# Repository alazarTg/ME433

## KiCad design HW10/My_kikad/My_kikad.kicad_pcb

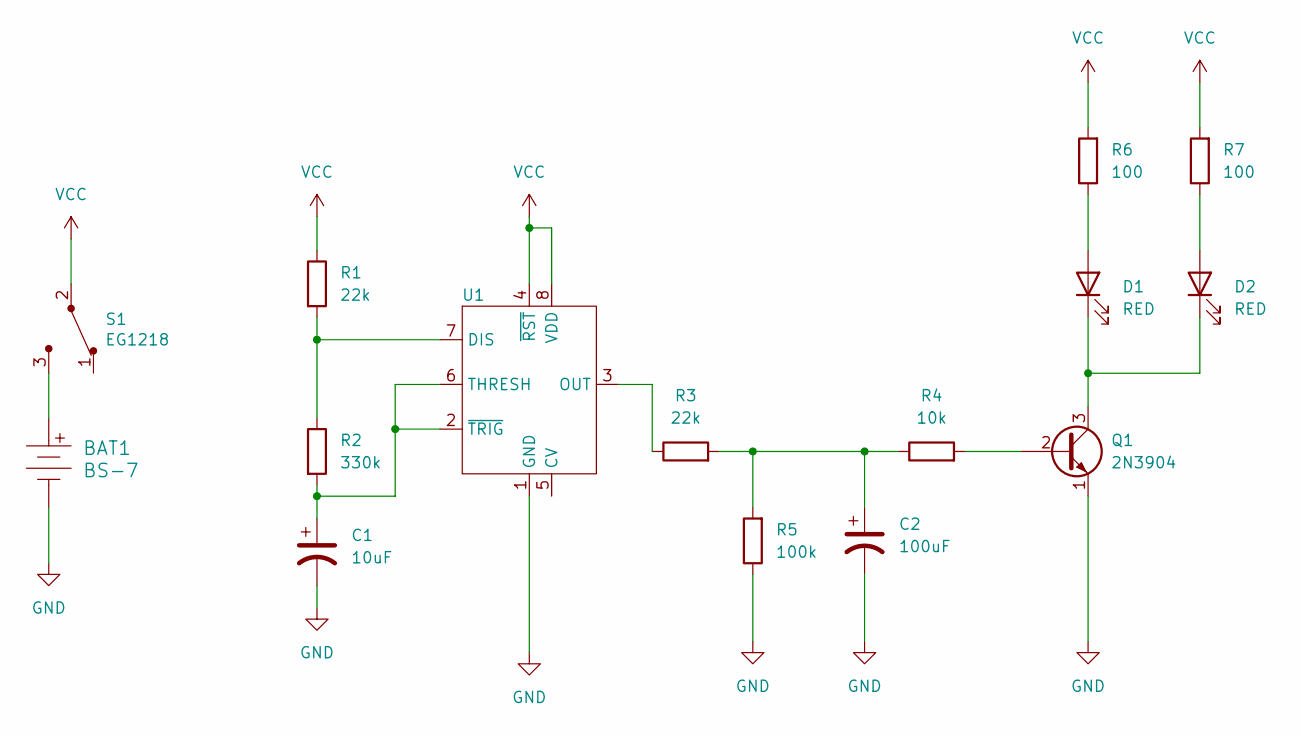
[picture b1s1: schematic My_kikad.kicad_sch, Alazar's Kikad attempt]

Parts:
BAT1: BS-7; Battery_Holder_Coin_2032_BS-7; MPN BS-7; Digi-Key_PN BS-7-ND
C1: 10uF; CP_Radial_D5.0mm_P2.00mm
C2: 100uF; CP_Radial_D6.3mm_P2.50mm
D1, D2: RED; LED_D3.0mm
Q1: 2N3904; TO-92-3
R1, R3: 22k; R_Axial_DIN0207_L6.3mm_D2.5mm_P7.62mm_Horizontal
R2: 330k; R_Axial_DIN0207_L6.3mm_D2.5mm_P7.62mm_Horizontal
R4: 10k; R_Axial_DIN0207_L6.3mm_D2.5mm_P7.62mm_Horizontal
R5: 100k; R_Axial_DIN0207_L6.3mm_D2.5mm_P7.62mm_Horizontal
R6, R7: 100; R_Axial_DIN0207_L6.3mm_D2.5mm_P7.62mm_Horizontal
S1: EG1218; Switch_Slide_11.6x4mm_EG1218; MPN EG1218; Digi-Key_PN EG1903-ND
U1: ICM7555_PDIP

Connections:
GND: BAT1.Neg, C1.2, C2.2, Q1.1 (E), R5.1, U1.1 (GND); also elsewhere on the board
unnamed: BAT1.Pos, S1.3
unnamed: C2.1, R3.2, R4.1, R5.2
unnamed: D1.2 (A), R6.1
unnamed: D1.1 (K), D2.1 (K), Q1.3 (C)
unnamed: D2.2 (A), R7.1
unnamed: Q1.2 (B), R4.2
unnamed 7: R1.2, R2.1, U1.7 (DIS); also elsewhere on the board
unnamed 8: R3.1, U1.3 (OUT); also elsewhere on the board
unnamed 9: C1.1, R2.2, U1.2 (~TRIG), U1.6 (THRESH); also elsewhere on the board
VCC: R1.1, R6.2, R7.2, S1.2, U1.4 (~RST), U1.8 (VDD); also elsewhere on the board

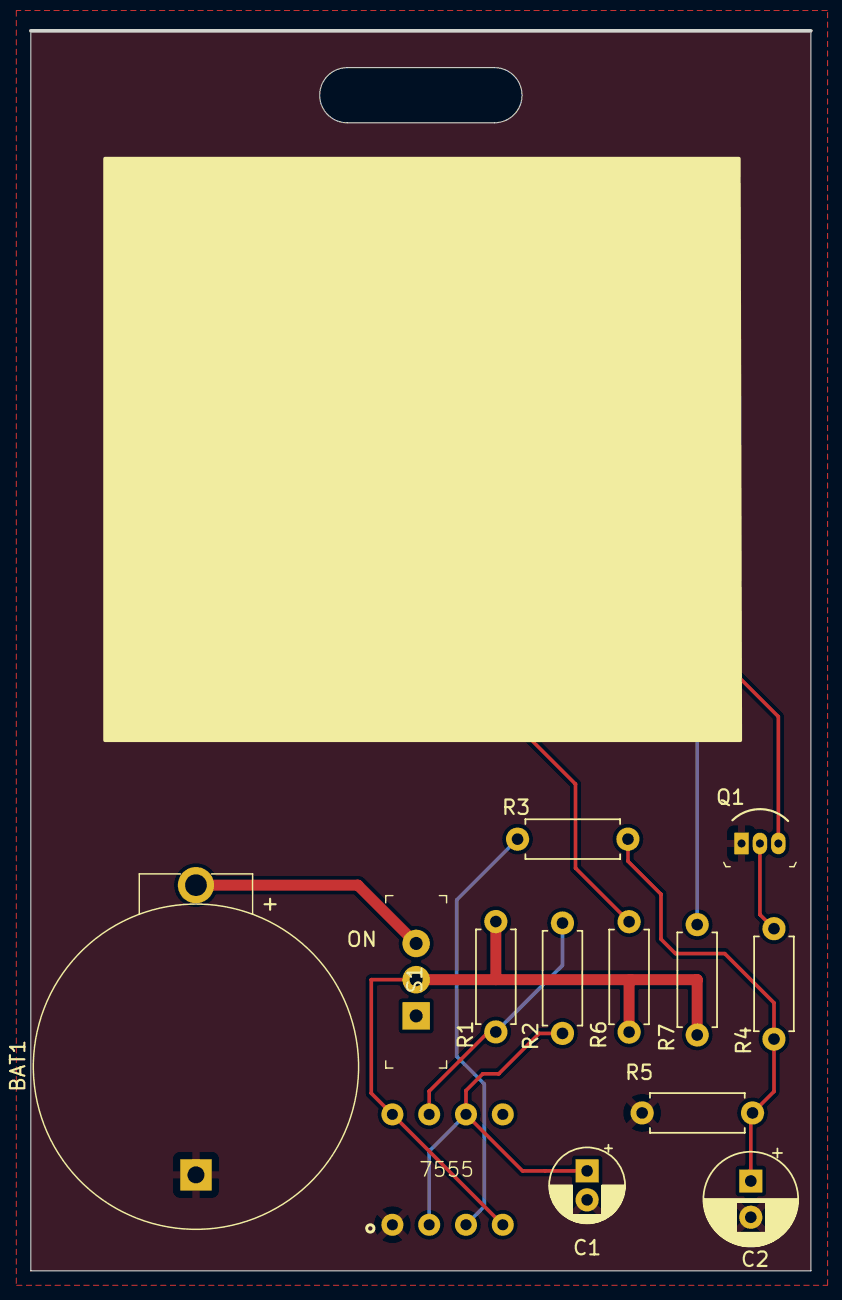
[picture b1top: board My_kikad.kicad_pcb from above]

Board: 2 copper layers, 53.8 x 85.6 mm, 15 parts (0 on the bottom side), 11 nets.

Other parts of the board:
7555: ICM7555_PDIP

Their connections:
GND: 7555.1 (GND); also elsewhere on the board
unnamed 7: 7555.7 (DIS); also elsewhere on the board
unnamed 8: 7555.3 (OUT); also elsewhere on the board
unnamed 9: 7555.2 (~TRIG), 7555.6 (THRESH); also elsewhere on the board
VCC: 7555.4 (~RST), 7555.8 (VDD); also elsewhere on the board

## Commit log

2024-04-02 Create HW2 folder
2024-04-02 Main code added
2024-04-02 Added new CMake files
2024-04-03 Added HW3
2024-04-08 Created HW4
2024-04-11 Working HW4
2024-04-11 Output of 1Hz triangle wave
2024-04-11 Rename 2D33F0F4-EC64-4426-A3EA-FE52D8D23AA6_4_5005_c.jpeg to Triangle_wave
2024-04-11 2Hz sine wave
2024-04-11 Rename 9A17AC0D-39B7-4D54-A99B-E5881B4510E3.jpeg to Sine Wave
2024-04-11 Adding picture of 2Hz sine wave
2024-04-11 Adding picture of 1Hz triangle wave
2024-04-13 Working HW5
2024-05-15 Added HW6
2024-05-21 HW9 added
2024-05-21 Python code running on the Zero
2024-05-22 add HW12
2024-05-24 Uploading HW16
2024-05-25 adding HW 15
2024-05-25 adding 3D printed robot
2024-05-25 Rename IMG_9264.jpeg to 3d printed.jpeg
2024-05-30 Done HW10
2024-05-30 Added HW17
2024-05-30 Finished Final project
